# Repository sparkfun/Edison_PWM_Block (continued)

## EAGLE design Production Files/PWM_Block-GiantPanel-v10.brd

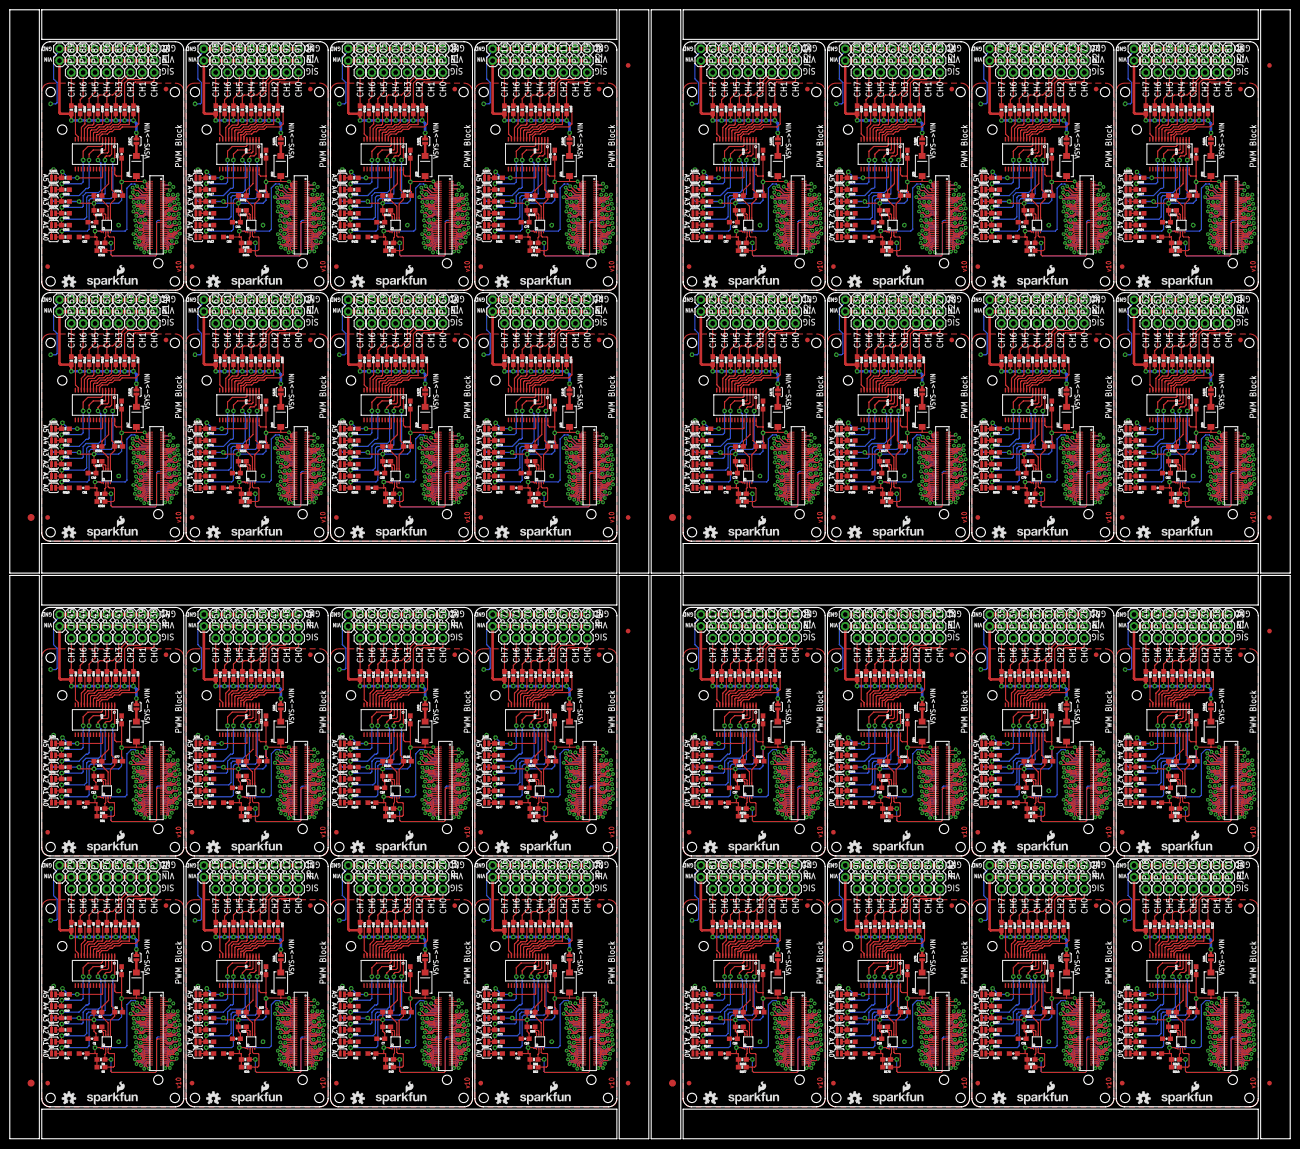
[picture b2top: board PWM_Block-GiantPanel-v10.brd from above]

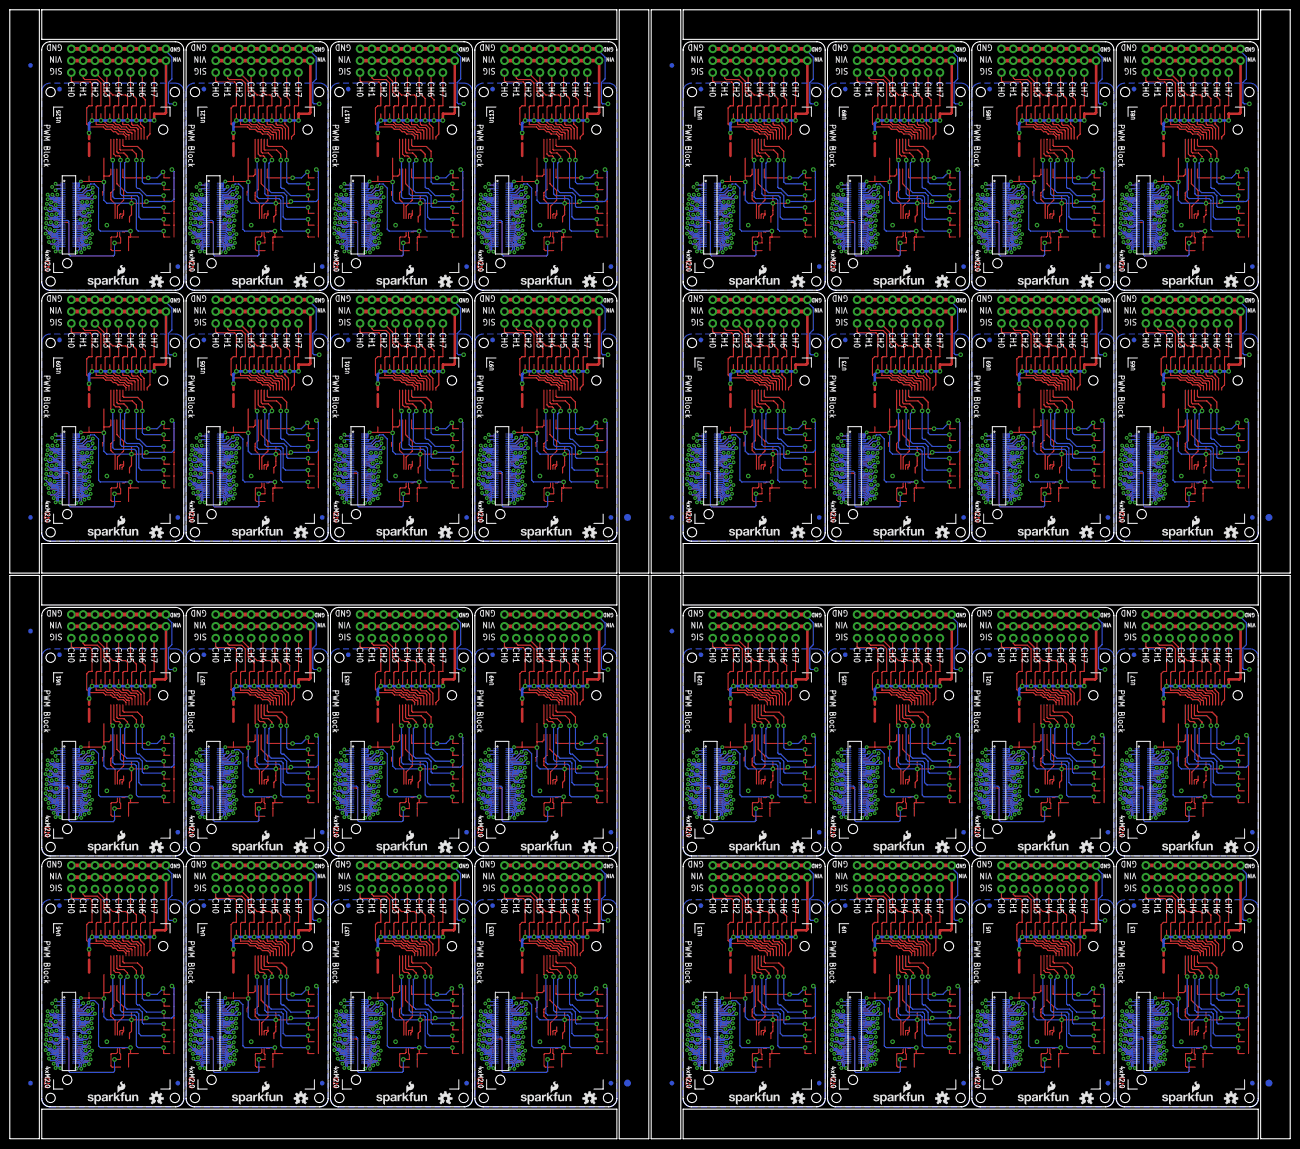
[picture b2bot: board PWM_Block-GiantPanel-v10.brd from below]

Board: 2 copper layers, 274.8 x 242.3 mm, 1656 parts (204 on the bottom side), 2464 nets.

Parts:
C1, C2, C3, C4, C5, C6, C7, C8, C9, C10, C11, C12, C13, C14, C15, C16, C17, C18, C19, C20, C21, C22, C23, C24, C25, C26, C27, C28, C29, C30, C31, C32, C33, C34, C35, C36, C37, C38, C39, C40, C41, C42, C43, C44, C45, C46, C47, C48, C49, C50, C51, C52, C53, C54, C55, C56, C57, C58, C59, C60, C61, C62, C63, C64, C65, C66, C67, C68, C69, C70, C71, C72, C73, C74, C75, C76, C77, C78, C79, C80, C81, C82, C83, C84, C85, C86, C87, C88, C89, C90, C91, C92, C93, C94, C95, C96: 0.1uF; 0603-CAP
D1, D2, D3, D4, D5, D6, D7, D8, D9, D10, D11, D12, D13, D14, D15, D16, D17, D18, D19, D20, D21, D22, D23, D24, D25, D26, D27, D28, D29, D30, D31, D32: B340A; SMA-DIODE
E$1, E$2, E$9, E$10, E$15, E$16, E$21, E$22: FIDUCIAL-1.5X3
E$3, E$4, E$5, E$6, E$7, E$8, E$11, E$12, E$13, E$14, E$17, E$18, E$19, E$20, E$23, E$24: FIDUCIAL-1X2
FID1, FID2, FID3, FID4, FID5, FID6, FID7, FID8, FID9, FID10, FID11, FID12, FID13, FID14, FID15, FID16, FID17, FID18, FID19, FID20, FID21, FID22, FID23, FID24, FID25, FID26, FID27, FID28, FID29, FID30, FID31, FID32, FID33, FID34, FID35, FID36, FID37, FID38, FID39, FID40, FID41, FID42, FID43, FID44, FID45, FID46, FID47, FID48, FID49, FID50, FID51, FID52, FID53, FID54, FID55, FID56, FID57, FID58, FID59, FID60, FID61, FID62, FID63, FID64, FID65, FID66, FID67, FID68, FID69, FID70, FID71, FID72, FID73, FID74, FID75, FID76, FID77, FID78, FID79, FID80, FID81, FID82, FID83, FID84, FID85, FID86, FID87, FID88, FID89, FID90, FID91, FID92, FID93, FID94, FID95, FID96, FID97, FID98, FID99, FID100, FID101, FID102, FID103, FID104, FID105, FID106, FID107, FID108, FID109, FID110, FID111, FID112, FID113, FID114, FID115, FID116, FID117, FID118, FID119, FID120, FID121, FID122, FID123, FID124, FID125, FID126, FID127, FID128: FIDUCIAL1X2; FIDUCIAL-1X2
JP1, JP2, JP3, JP4, JP5, JP6, JP7, JP8, JP10, JP11, JP12, JP13, JP14, JP15, JP16, JP17, JP19, JP20, JP21, JP22, JP23, JP24, JP25, JP26, JP28, JP29, JP30, JP31, JP32, JP33, JP34, JP35, JP37, JP38, JP39, JP40, JP41, JP42, JP43, JP44, JP46, JP47, JP48, JP49, JP50, JP51, JP52, JP53, JP55, JP56, JP57, JP58, JP59, JP60, JP61, JP62, JP64, JP65, JP66, JP67, JP68, JP69, JP70, JP71, JP73, JP74, JP75, JP76, JP77, JP78, JP79, JP80, JP82, JP83, JP84, JP85, JP86, JP87, JP88, JP89, JP91, JP92, JP93, JP94, JP95, JP96, JP97, JP98, JP100, JP101, JP102, JP103, JP104, JP105, JP106, JP107, JP109, JP110, JP111, JP112, JP113, JP114, JP115, JP116, JP118, JP119, JP120, JP121, JP122, JP123, JP124, JP125, JP127, JP128, JP129, JP130, JP131, JP132, JP133, JP134, JP136, JP137, JP138, JP139, JP140, JP141, JP142, JP143, JP145, JP146, JP147, JP148, JP149, JP150, JP151, JP152, JP154, JP155, JP156, JP157, JP158, JP159, JP160, JP161, JP163, JP164, JP165, JP166, JP167, JP168, JP169, JP170, JP172, JP173, JP174, JP175, JP176, JP177, JP178, JP179, JP181, JP182, JP183, JP184, JP185, JP186, JP187, JP188, JP190, JP191, JP192, JP193, JP194, JP195, JP196, JP197, JP199, JP200, JP201, JP202, JP203, JP204, JP205, JP206, JP208, JP209, JP210, JP211, JP212, JP213, JP214, JP215, JP217, JP218, JP219, JP220, JP221, JP222, JP223, JP224, JP226, JP227, JP228, JP229, JP230, JP231, JP232, JP233, JP235, JP236, JP237, JP238, JP239, JP240, JP241, JP242, JP244, JP245, JP246, JP247, JP248, JP249, JP250, JP251, JP253, JP254, JP255, JP256, JP257, JP258, JP259, JP260, JP262, JP263, JP264, JP265, JP266, JP267, JP268, JP269, JP271, JP272, JP273, JP274, JP275, JP276, JP277, JP278, JP280, JP281, JP282, JP283, JP284, JP285, JP286, JP287: 1X03
JP9, JP18, JP27, JP36, JP45, JP54, JP63, JP72, JP81, JP90, JP99, JP108, JP117, JP126, JP135, JP144, JP153, JP162, JP171, JP180, JP189, JP198, JP207, JP216, JP225, JP234, JP243, JP252, JP261, JP270, JP279, JP288: M02PTH; 1X02
LOGO1, LOGO3, LOGO6, LOGO7, LOGO10, LOGO11, LOGO14, LOGO15, LOGO18, LOGO19, LOGO22, LOGO23, LOGO26, LOGO27, LOGO30, LOGO31, LOGO34, LOGO35, LOGO38, LOGO39, LOGO42, LOGO43, LOGO46, LOGO47, LOGO50, LOGO51, LOGO54, LOGO55, LOGO58, LOGO59, LOGO62, LOGO63, LOGO66, LOGO67, LOGO70, LOGO71, LOGO74, LOGO75, LOGO78, LOGO79, LOGO82, LOGO83, LOGO86, LOGO87, LOGO90, LOGO91, LOGO94, LOGO95, LOGO98, LOGO99, LOGO102, LOGO103, LOGO106, LOGO107, LOGO110, LOGO111, LOGO114, LOGO115, LOGO118, LOGO119, LOGO122, LOGO123, LOGO126, LOGO127: SFE_LOGO_NAME_FLAME.1_INCH; SFE_LOGO_NAME_FLAME_.1
LOGO2, LOGO4, LOGO5, LOGO8, LOGO9, LOGO12, LOGO13, LOGO16, LOGO17, LOGO20, LOGO21, LOGO24, LOGO25, LOGO28, LOGO29, LOGO32, LOGO33, LOGO36, LOGO37, LOGO40, LOGO41, LOGO44, LOGO45, LOGO48, LOGO49, LOGO52, LOGO53, LOGO56, LOGO57, LOGO60, LOGO61, LOGO64, LOGO65, LOGO68, LOGO69, LOGO72, LOGO73, LOGO76, LOGO77, LOGO80, LOGO81, LOGO84, LOGO85, LOGO88, LOGO89, LOGO92, LOGO93, LOGO96, LOGO97, LOGO100, LOGO101, LOGO104, LOGO105, LOGO108, LOGO109, LOGO112, LOGO113, LOGO116, LOGO117, LOGO120, LOGO121, LOGO124, LOGO125, LOGO128: OSHW-LOGOS; OSHW-LOGO-S
R1, R2, R20, R21, R39, R40, R58, R59, R77, R78, R96, R97, R115, R116, R134, R135, R153, R154, R172, R173, R191, R192, R210, R211, R229, R230, R248, R249, R267, R268, R286, R287, R305, R306, R324, R325, R343, R344, R362, R363, R381, R382, R400, R401, R419, R420, R438, R439, R457, R458, R476, R477, R495, R496, R514, R515, R533, R534, R552, R553, R571, R572, R590, R591: 10K; 0603-RES
R3, R22, R41, R60, R79, R98, R117, R136, R155, R174, R193, R212, R231, R250, R269, R288, R307, R326, R345, R364, R383, R402, R421, R440, R459, R478, R497, R516, R535, R554, R573, R592: 200k; 0603-RES
R4, R5, R23, R24, R42, R43, R61, R62, R80, R81, R99, R100, R118, R119, R137, R138, R156, R157, R175, R176, R194, R195, R213, R214, R232, R233, R251, R252, R270, R271, R289, R290, R308, R309, R327, R328, R346, R347, R365, R366, R384, R385, R403, R404, R422, R423, R441, R442, R460, R461, R479, R480, R498, R499, R517, R518, R536, R537, R555, R556, R574, R575, R593, R594: DNP; 0603-RES
R6, R7, R8, R9, R10, R11, R12, R13, R14, R15, R16, R17, R18, R19, R25, R26, R27, R28, R29, R30, R31, R32, R33, R34, R35, R36, R37, R38, R44, R45, R46, R47, R48, R49, R50, R51, R52, R53, R54, R55, R56, R57, R63, R64, R65, R66, R67, R68, R69, R70, R71, R72, R73, R74, R75, R76, R82, R83, R84, R85, R86, R87, R88, R89, R90, R91, R92, R93, R94, R95, R101, R102, R103, R104, R105, R106, R107, R108, R109, R110, R111, R112, R113, R114, R120, R121, R122, R123, R124, R125, R126, R127, R128, R129, R130, R131, R132, R133, R139, R140, R141, R142, R143, R144, R145, R146, R147, R148, R149, R150, R151, R152, R158, R159, R160, R161, R162, R163, R164, R165, R166, R167, R168, R169, R170, R171, R177, R178, R179, R180, R181, R182, R183, R184, R185, R186, R187, R188, R189, R190, R196, R197, R198, R199, R200, R201, R202, R203, R204, R205, R206, R207, R208, R209, R215, R216, R217, R218, R219, R220, R221, R222, R223, R224, R225, R226, R227, R228, R234, R235, R236, R237, R238, R239, R240, R241, R242, R243, R244, R245, R246, R247, R253, R254, R255, R256, R257, R258, R259, R260, R261, R262, R263, R264, R265, R266, R272, R273, R274, R275, R276, R277, R278, R279, R280, R281, R282, R283, R284, R285, R291, R292, R293, R294, R295, R296, R297, R298, R299, R300, R301, R302, R303, R304, R310, R311, R312, R313, R314, R315, R316, R317, R318, R319, R320, R321, R322, R323, R329, R330, R331, R332, R333, R334, R335, R336, R337, R338, R339, R340, R341, R342, R348, R349, R350, R351, R352, R353, R354, R355, R356, R357, R358, R359, R360, R361, R367, R368, R369, R370, R371, R372, R373, R374, R375, R376, R377, R378, R379, R380, R386, R387, R388, R389, R390, R391, R392, R393, R394, R395, R396, R397, R398, R399, R405, R406, R407, R408, R409, R410, R411, R412, R413, R414, R415, R416, R417, R418, R424, R425, R426, R427, R428, R429, R430, R431, R432, R433, R434, R435, R436, R437, R443, R444, R445, R446, R447, R448, R449, R450, R451, R452, R453, R454, R455, R456, R462, R463, R464, R465, R466, R467, R468, R469, R470, R471, R472, R473, R474, R475, R481, R482, R483, R484, R485, R486, R487, R488, R489, R490, R491, R492, R493, R494, R500, R501, R502, R503, R504, R505, R506, R507, R508, R509, R510, R511, R512, R513, R519, R520, R521, R522, R523, R524, R525, R526, R527, R528, R529, R530, R531, R532, R538, R539, R540, R541, R542, R543, R544, R545, R546, R547, R548, R549, R550, R551, R557, R558, R559, R560, R561, R562, R563, R564, R565, R566, R567, R568, R569, R570, R576, R577, R578, R579, R580, R581, R582, R583, R584, R585, R586, R587, R588, R589, R595, R596, R597, R598, R599, R600, R601, R602, R603, R604, R605, R606, R607, R608: 1K; 0603-RES
SJ1, SJ2, SJ3, SJ4, SJ5, SJ6, SJ8, SJ9, SJ10, SJ11, SJ12, SJ13, SJ15, SJ16, SJ17, SJ18, SJ19, SJ20, SJ22, SJ23, SJ24, SJ25, SJ26, SJ27, SJ29, SJ30, SJ31, SJ32, SJ33, SJ34, SJ36, SJ37, SJ38, SJ39, SJ40, SJ41, SJ43, SJ44, SJ45, SJ46, SJ47, SJ48, SJ50, SJ51, SJ52, SJ53, SJ54, SJ55, SJ57, SJ58, SJ59, SJ60, SJ61, SJ62, SJ64, SJ65, SJ66, SJ67, SJ68, SJ69, SJ71, SJ72, SJ73, SJ74, SJ75, SJ76, SJ78, SJ79, SJ80, SJ81, SJ82, SJ83, SJ85, SJ86, SJ87, SJ88, SJ89, SJ90, SJ92, SJ93, SJ94, SJ95, SJ96, SJ97, SJ99, SJ100, SJ101, SJ102, SJ103, SJ104, SJ106, SJ107, SJ108, SJ109, SJ110, SJ111, SJ113, SJ114, SJ115, SJ116, SJ117, SJ118, SJ120, SJ121, SJ122, SJ123, SJ124, SJ125, SJ127, SJ128, SJ129, SJ130, SJ131, SJ132, SJ134, SJ135, SJ136, SJ137, SJ138, SJ139, SJ141, SJ142, SJ143, SJ144, SJ145, SJ146, SJ148, SJ149, SJ150, SJ151, SJ152, SJ153, SJ155, SJ156, SJ157, SJ158, SJ159, SJ160, SJ162, SJ163, SJ164, SJ165, SJ166, SJ167, SJ169, SJ170, SJ171, SJ172, SJ173, SJ174, SJ176, SJ177, SJ178, SJ179, SJ180, SJ181, SJ183, SJ184, SJ185, SJ186, SJ187, SJ188, SJ190, SJ191, SJ192, SJ193, SJ194, SJ195, SJ197, SJ198, SJ199, SJ200, SJ201, SJ202, SJ204, SJ205, SJ206, SJ207, SJ208, SJ209, SJ211, SJ212, SJ213, SJ214, SJ215, SJ216, SJ218, SJ219, SJ220, SJ221, SJ222, SJ223: JUMPER-PAD-2-NOYES_SILK; PAD-JUMPER-2-NO_YES_SILK
SJ7, SJ14, SJ21, SJ28, SJ35, SJ42, SJ49, SJ56, SJ63, SJ70, SJ77, SJ84, SJ91, SJ98, SJ105, SJ112, SJ119, SJ126, SJ133, SJ140, SJ147, SJ154, SJ161, SJ168, SJ175, SJ182, SJ189, SJ196, SJ203, SJ210, SJ217, SJ224: VIN_ENABLE; PAD-JUMPER-2-NO_YES_SILK
U1, U8, U12, U16, U20, U24, U28, U32, U36, U40, U44, U48, U52, U56, U60, U64, U68, U72, U76, U80, U84, U88, U92, U96, U100, U104, U108, U112, U116, U120, U124, U128: PCA9685; TSSOP-28_4MM
U2, U7, U11, U15, U19, U23, U27, U31, U35, U39, U43, U47, U51, U55, U59, U63, U67, U71, U75, U79, U83, U87, U91, U95, U99, U103, U107, U111, U115, U119, U123, U127: PCA9306; PCA9306DC-1:1
U3, U5, U9, U13, U17, U21, U25, U29, U33, U37, U41, U45, U49, U53, U57, U61, U65, U69, U73, U77, U81, U85, U89, U93, U97, U101, U105, U109, U113, U117, U121, U125: EDISON_CONNECTOR_FULLMOUNTING_HOLES; EDISON_DAUGHTER
U4, U6, U10, U14, U18, U22, U26, U30, U34, U38, U42, U46, U50, U54, U58, U62, U66, U70, U74, U78, U82, U86, U90, U94, U98, U102, U106, U110, U114, U118, U122, U126: EDISON_CONNECTOR_FULLHEADER; DF40C-70DP-0.4(51)

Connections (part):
1.8V: C3.1, R4.2, R5.2, U2.1, U3.12, U4.12
1.8V1: C6.1, R23.2, R24.2, U5.12, U6.12, U7.1
1.8V2: C9.1, R42.2, R43.2, U9.12, U10.12, U11.1
1.8V3: C12.1, R61.2, R62.2, U13.12, U14.12, U15.1
1.8V4: C15.1, R80.2, R81.2, U17.12, U18.12, U19.1
1.8V5: C18.1, R99.2, R100.2, U21.12, U22.12, U23.1
1.8V6: C21.1, R118.2, R119.2, U25.12, U26.12, U27.1
1.8V7: C24.1, R137.2, R138.2, U29.12, U30.12, U31.1
1.8V8: C27.1, R156.2, R157.2, U33.12, U34.12, U35.1
1.8V9: C30.1, R175.2, R176.2, U37.12, U38.12, U39.1
1.8V10: C33.1, R194.2, R195.2, U41.12, U42.12, U43.1
1.8V11: C36.1, R213.2, R214.2, U45.12, U46.12, U47.1
1.8V12: C39.1, R232.2, R233.2, U49.12, U50.12, U51.1
1.8V13: C42.1, R251.2, R252.2, U53.12, U54.12, U55.1
1.8V14: C45.1, R270.2, R271.2, U57.12, U58.12, U59.1
1.8V15: C48.1, R289.2, R290.2, U61.12, U62.12, U63.1
1.8V16: C51.1, R308.2, R309.2, U65.12, U66.12, U67.1
1.8V17: C54.1, R327.2, R328.2, U69.12, U70.12, U71.1
1.8V18: C57.1, R346.2, R347.2, U73.12, U74.12, U75.1
1.8V19: C60.1, R365.2, R366.2, U77.12, U78.12, U79.1
1.8V20: C63.1, R384.2, R385.2, U81.12, U82.12, U83.1
1.8V21: C66.1, R403.2, R404.2, U85.12, U86.12, U87.1
1.8V22: C69.1, R422.2, R423.2, U89.12, U90.12, U91.1
1.8V23: C72.1, R441.2, R442.2, U93.12, U94.12, U95.1
1.8V24: C75.1, R460.2, R461.2, U97.12, U98.12, U99.1
1.8V25: C78.1, R479.2, R480.2, U101.12, U102.12, U103.1
1.8V26: C81.1, R498.2, R499.2, U105.12, U106.12, U107.1
1.8V27: C84.1, R517.2, R518.2, U109.12, U110.12, U111.1
1.8V28: C87.1, R536.2, R537.2, U113.12, U114.12, U115.1
1.8V29: C90.1, R555.2, R556.2, U117.12, U118.12, U119.1
1.8V30: C93.1, R574.2, R575.2, U121.12, U122.12, U123.1
1.8V31: C96.1, R593.2, R594.2, U125.12, U126.12, U127.1
3.3V: U3.8, U3.10, U4.8, U4.10
3.3V1: U5.8, U5.10, U6.8, U6.10
3.3V2: U9.8, U9.10, U10.8, U10.10
3.3V3: U13.8, U13.10, U14.8, U14.10
3.3V4: U17.8, U17.10, U18.8, U18.10
3.3V5: U21.8, U21.10, U22.8, U22.10
3.3V6: U25.8, U25.10, U26.8, U26.10
3.3V7: U29.8, U29.10, U30.8, U30.10
3.3V8: U33.8, U33.10, U34.8, U34.10
3.3V9: U37.8, U37.10, U38.8, U38.10
3.3V10: U41.8, U41.10, U42.8, U42.10
3.3V11: U45.8, U45.10, U46.8, U46.10
3.3V12: U49.8, U49.10, U50.8, U50.10
3.3V13: U53.8, U53.10, U54.8, U54.10
3.3V14: U57.8, U57.10, U58.8, U58.10
3.3V15: U61.8, U61.10, U62.8, U62.10
3.3V16: U65.8, U65.10, U66.8, U66.10
3.3V17: U69.8, U69.10, U70.8, U70.10
3.3V18: U73.8, U73.10, U74.8, U74.10
3.3V19: U77.8, U77.10, U78.8, U78.10
3.3V20: U81.8, U81.10, U82.8, U82.10
3.3V21: U85.8, U85.10, U86.8, U86.10
3.3V22: U89.8, U89.10, U90.8, U90.10
3.3V23: U93.8, U93.10, U94.8, U94.10
3.3V24: U97.8, U97.10, U98.8, U98.10
3.3V25: U101.8, U101.10, U102.8, U102.10
3.3V26: U105.8, U105.10, U106.8, U106.10
3.3V27: U109.8, U109.10, U110.8, U110.10
3.3V28: U113.8, U113.10, U114.8, U114.10
3.3V29: U117.8, U117.10, U118.8, U118.10
3.3V30: U121.8, U121.10, U122.8, U122.10
3.3V31: U125.8, U125.10, U126.8, U126.10
A0: R14.2, SJ1.2, U1.1
A1: R15.2, SJ2.2, U1.2
A2: R16.2, SJ3.2, U1.3
A3: R17.2, SJ4.2, U1.4
A4: R18.2, SJ5.2, U1.5
A5: R19.2, SJ6.2, U1.24
A6: R37.2, SJ12.2, U8.5
A7: R36.2, SJ11.2, U8.4
A8: R35.2, SJ10.2, U8.3
A9: R34.2, SJ9.2, U8.2
A10: R33.2, SJ8.2, U8.1
A11: R38.2, SJ13.2, U8.24
A12: R56.2, SJ19.2, U12.5
A13: R55.2, SJ18.2, U12.4
A14: R54.2, SJ17.2, U12.3
A15: R53.2, SJ16.2, U12.2
A16: R52.2, SJ15.2, U12.1
A17: R57.2, SJ20.2, U12.24
A18: R75.2, SJ26.2, U16.5
A19: R74.2, SJ25.2, U16.4
A20: R73.2, SJ24.2, U16.3
A21: R72.2, SJ23.2, U16.2
A22: R71.2, SJ22.2, U16.1
A23: R76.2, SJ27.2, U16.24
A24: R94.2, SJ33.2, U20.5
A25: R93.2, SJ32.2, U20.4
A26: R92.2, SJ31.2, U20.3
A27: R91.2, SJ30.2, U20.2
A28: R90.2, SJ29.2, U20.1
A29: R95.2, SJ34.2, U20.24
A30: R113.2, SJ40.2, U24.5
A31: R112.2, SJ39.2, U24.4
A32: R111.2, SJ38.2, U24.3
A33: R110.2, SJ37.2, U24.2
A34: R109.2, SJ36.2, U24.1
A35: R114.2, SJ41.2, U24.24
A36: R132.2, SJ47.2, U28.5
A37: R131.2, SJ46.2, U28.4
A38: R130.2, SJ45.2, U28.3
A39: R129.2, SJ44.2, U28.2
A40: R128.2, SJ43.2, U28.1
A41: R133.2, SJ48.2, U28.24
A42: R151.2, SJ54.2, U32.5
A43: R150.2, SJ53.2, U32.4
A44: R149.2, SJ52.2, U32.3
A45: R148.2, SJ51.2, U32.2
A46: R147.2, SJ50.2, U32.1
A47: R152.2, SJ55.2, U32.24
A48: R170.2, SJ61.2, U36.5
A49: R169.2, SJ60.2, U36.4
A50: R168.2, SJ59.2, U36.3
A51: R167.2, SJ58.2, U36.2
A52: R166.2, SJ57.2, U36.1
A53: R171.2, SJ62.2, U36.24
A54: R189.2, SJ68.2, U40.5
A55: R188.2, SJ67.2, U40.4
A56: R187.2, SJ66.2, U40.3
A57: R186.2, SJ65.2, U40.2
A58: R185.2, SJ64.2, U40.1
A59: R190.2, SJ69.2, U40.24
A60: R208.2, SJ75.2, U44.5
A61: R207.2, SJ74.2, U44.4
A62: R206.2, SJ73.2, U44.3
A63: R205.2, SJ72.2, U44.2
A64: R204.2, SJ71.2, U44.1
A65: R209.2, SJ76.2, U44.24
A66: R227.2, SJ82.2, U48.5
A67: R226.2, SJ81.2, U48.4
A68: R225.2, SJ80.2, U48.3
A69: R224.2, SJ79.2, U48.2
A70: R223.2, SJ78.2, U48.1
A71: R228.2, SJ83.2, U48.24
A72: R246.2, SJ89.2, U52.5
A73: R245.2, SJ88.2, U52.4
A74: R244.2, SJ87.2, U52.3
A75: R243.2, SJ86.2, U52.2
A76: R242.2, SJ85.2, U52.1
A77: R247.2, SJ90.2, U52.24
A78: R265.2, SJ96.2, U56.5
A79: R264.2, SJ95.2, U56.4
A80: R263.2, SJ94.2, U56.3
A81: R262.2, SJ93.2, U56.2
A82: R261.2, SJ92.2, U56.1
A83: R266.2, SJ97.2, U56.24
A84: R284.2, SJ103.2, U60.5
A85: R283.2, SJ102.2, U60.4
A86: R282.2, SJ101.2, U60.3
A87: R281.2, SJ100.2, U60.2
A88: R280.2, SJ99.2, U60.1
A89: R285.2, SJ104.2, U60.24
A90: R303.2, SJ110.2, U64.5
A91: R302.2, SJ109.2, U64.4
A92: R301.2, SJ108.2, U64.3
A93: R300.2, SJ107.2, U64.2
A94: R299.2, SJ106.2, U64.1
A95: R304.2, SJ111.2, U64.24
A96: R322.2, SJ117.2, U68.5
A97: R321.2, SJ116.2, U68.4
A98: R320.2, SJ115.2, U68.3
A99: R319.2, SJ114.2, U68.2
A100: R318.2, SJ113.2, U68.1
A101: R323.2, SJ118.2, U68.24
A102: R341.2, SJ124.2, U72.5
A103: R340.2, SJ123.2, U72.4
A104: R339.2, SJ122.2, U72.3
A105: R338.2, SJ121.2, U72.2
A106: R337.2, SJ120.2, U72.1
A107: R342.2, SJ125.2, U72.24
A108: R360.2, SJ131.2, U76.5
A109: R359.2, SJ130.2, U76.4
A110: R358.2, SJ129.2, U76.3
A111: R357.2, SJ128.2, U76.2
A112: R356.2, SJ127.2, U76.1
A113: R361.2, SJ132.2, U76.24
A114: R379.2, SJ138.2, U80.5
A115: R378.2, SJ137.2, U80.4
A116: R377.2, SJ136.2, U80.3
A117: R376.2, SJ135.2, U80.2
A118: R375.2, SJ134.2, U80.1
A119: R380.2, SJ139.2, U80.24
A120: R398.2, SJ145.2, U84.5
A121: R397.2, SJ144.2, U84.4
A122: R396.2, SJ143.2, U84.3
A123: R395.2, SJ142.2, U84.2
A124: R394.2, SJ141.2, U84.1
A125: R399.2, SJ146.2, U84.24
A126: R417.2, SJ152.2, U88.5
A127: R416.2, SJ151.2, U88.4
A128: R415.2, SJ150.2, U88.3
A129: R414.2, SJ149.2, U88.2
A130: R413.2, SJ148.2, U88.1
A131: R418.2, SJ153.2, U88.24
A132: R436.2, SJ159.2, U92.5
A133: R435.2, SJ158.2, U92.4
A134: R434.2, SJ157.2, U92.3
A135: R433.2, SJ156.2, U92.2
A136: R432.2, SJ155.2, U92.1
A137: R437.2, SJ160.2, U92.24
A138: R455.2, SJ166.2, U96.5
A139: R454.2, SJ165.2, U96.4
A140: R453.2, SJ164.2, U96.3
A141: R452.2, SJ163.2, U96.2
A142: R451.2, SJ162.2, U96.1
A143: R456.2, SJ167.2, U96.24
A144: R474.2, SJ173.2, U100.5
A145: R473.2, SJ172.2, U100.4
A146: R472.2, SJ171.2, U100.3
A147: R471.2, SJ170.2, U100.2
A148: R470.2, SJ169.2, U100.1
A149: R475.2, SJ174.2, U100.24
A150: R493.2, SJ180.2, U104.5
A151: R492.2, SJ179.2, U104.4
A152: R491.2, SJ178.2, U104.3
A153: R490.2, SJ177.2, U104.2
A154: R489.2, SJ176.2, U104.1
A155: R494.2, SJ181.2, U104.24
A156: R512.2, SJ187.2, U108.5
A157: R511.2, SJ186.2, U108.4
A158: R510.2, SJ185.2, U108.3
A159: R509.2, SJ184.2, U108.2
A160: R508.2, SJ183.2, U108.1
A161: R513.2, SJ188.2, U108.24
A162: R531.2, SJ194.2, U112.5
A163: R530.2, SJ193.2, U112.4
A164: R529.2, SJ192.2, U112.3
A165: R528.2, SJ191.2, U112.2
A166: R527.2, SJ190.2, U112.1
A167: R532.2, SJ195.2, U112.24
A168: R550.2, SJ201.2, U116.5
A169: R549.2, SJ200.2, U116.4
A170: R548.2, SJ199.2, U116.3
A171: R547.2, SJ198.2, U116.2
A172: R546.2, SJ197.2, U116.1
A173: R551.2, SJ202.2, U116.24
A174: R569.2, SJ208.2, U120.5
A175: R568.2, SJ207.2, U120.4
A176: R567.2, SJ206.2, U120.3
A177: R566.2, SJ205.2, U120.2
A178: R565.2, SJ204.2, U120.1
A179: R570.2, SJ209.2, U120.24
A180: R588.2, SJ215.2, U124.5
A181: R587.2, SJ214.2, U124.4
A182: R586.2, SJ213.2, U124.3
A183: R585.2, SJ212.2, U124.2
A184: R584.2, SJ211.2, U124.1
A185: R589.2, SJ216.2, U124.24
A186: R607.2, SJ222.2, U128.5
A187: R606.2, SJ221.2, U128.4
A188: R605.2, SJ220.2, U128.3
A189: R604.2, SJ219.2, U128.2
A190: R603.2, SJ218.2, U128.1
A191: R608.2, SJ223.2, U128.24
CH0: JP1.3, R13.1, U1.6
CH1: JP2.3, R12.1, U1.7
CH2: JP3.3, R11.1, U1.8
CH3: JP4.3, R10.1, U1.9
CH4: JP5.3, R9.1, U1.10
CH5: JP6.3, R8.1, U1.11
CH6: JP7.3, R7.1, U1.12
CH7: JP8.3, R6.1, U1.13
CH8: JP10.3, R32.1, U8.6
CH9: JP11.3, R31.1, U8.7
CH10: JP12.3, R30.1, U8.8
CH11: JP13.3, R29.1, U8.9
CH12: JP14.3, R28.1, U8.10
CH13: JP15.3, R27.1, U8.11
CH14: JP16.3, R26.1, U8.12
CH15: JP17.3, R25.1, U8.13
CH16: JP19.3, R51.1, U12.6
CH17: JP20.3, R50.1, U12.7
CH18: JP21.3, R49.1, U12.8
CH19: JP22.3, R48.1, U12.9
CH20: JP23.3, R47.1, U12.10
CH21: JP24.3, R46.1, U12.11
CH22: JP25.3, R45.1, U12.12
CH23: JP26.3, R44.1, U12.13
CH24: JP28.3, R70.1, U16.6
CH25: JP29.3, R69.1, U16.7
CH26: JP30.3, R68.1, U16.8
CH27: JP31.3, R67.1, U16.9
CH28: JP32.3, R66.1, U16.10
CH29: JP33.3, R65.1, U16.11
CH30: JP34.3, R64.1, U16.12
CH31: JP35.3, R63.1, U16.13
CH32: JP37.3, R89.1, U20.6
CH33: JP38.3, R88.1, U20.7
CH34: JP39.3, R87.1, U20.8
CH35: JP40.3, R86.1, U20.9
CH36: JP41.3, R85.1, U20.10
CH37: JP42.3, R84.1, U20.11
CH38: JP43.3, R83.1, U20.12
CH39: JP44.3, R82.1, U20.13
CH40: JP46.3, R108.1, U24.6
CH41: JP47.3, R107.1, U24.7
CH42: JP48.3, R106.1, U24.8
CH43: JP49.3, R105.1, U24.9
CH44: JP50.3, R104.1, U24.10
CH45: JP51.3, R103.1, U24.11
CH46: JP52.3, R102.1, U24.12
CH47: JP53.3, R101.1, U24.13
CH48: JP55.3, R127.1, U28.6
CH49: JP56.3, R126.1, U28.7
CH50: JP57.3, R125.1, U28.8
CH51: JP58.3, R124.1, U28.9
CH52: JP59.3, R123.1, U28.10
CH53: JP60.3, R122.1, U28.11
CH54: JP61.3, R121.1, U28.12
CH55: JP62.3, R120.1, U28.13
CH56: JP64.3, R146.1, U32.6
CH57: JP65.3, R145.1, U32.7
CH58: JP66.3, R144.1, U32.8
CH59: JP67.3, R143.1, U32.9
CH60: JP68.3, R142.1, U32.10
CH61: JP69.3, R141.1, U32.11
CH62: JP70.3, R140.1, U32.12
CH63: JP71.3, R139.1, U32.13
CH64: JP73.3, R165.1, U36.6
CH65: JP74.3, R164.1, U36.7
CH66: JP75.3, R163.1, U36.8
CH67: JP76.3, R162.1, U36.9
CH68: JP77.3, R161.1, U36.10
CH69: JP78.3, R160.1, U36.11
CH70: JP79.3, R159.1, U36.12
CH71: JP80.3, R158.1, U36.13
CH72: JP82.3, R184.1, U40.6
CH73: JP83.3, R183.1, U40.7
CH74: JP84.3, R182.1, U40.8
CH75: JP85.3, R181.1, U40.9
CH76: JP86.3, R180.1, U40.10
CH77: JP87.3, R179.1, U40.11
CH78: JP88.3, R178.1, U40.12
CH79: JP89.3, R177.1, U40.13
CH80: JP91.3, R203.1, U44.6
CH81: JP92.3, R202.1, U44.7
CH82: JP93.3, R201.1, U44.8
CH83: JP94.3, R200.1, U44.9
CH84: JP95.3, R199.1, U44.10
CH85: JP96.3, R198.1, U44.11
CH86: JP97.3, R197.1, U44.12
CH87: JP98.3, R196.1, U44.13
CH88: JP100.3, R222.1, U48.6
CH89: JP101.3, R221.1, U48.7
CH90: JP102.3, R220.1, U48.8
CH91: JP103.3, R219.1, U48.9
CH92: JP104.3, R218.1, U48.10
CH93: JP105.3, R217.1, U48.11
CH94: JP106.3, R216.1, U48.12
CH95: JP107.3, R215.1, U48.13
CH96: JP109.3, R241.1, U52.6
CH97: JP110.3, R240.1, U52.7
CH98: JP111.3, R239.1, U52.8
CH99: JP112.3, R238.1, U52.9
CH100: JP113.3, R237.1, U52.10
CH101: JP114.3, R236.1, U52.11
CH102: JP115.3, R235.1, U52.12
CH103: JP116.3, R234.1, U52.13
CH104: JP118.3, R260.1, U56.6
CH105: JP119.3, R259.1, U56.7
CH106: JP120.3, R258.1, U56.8
CH107: JP121.3, R257.1, U56.9
CH108: JP122.3, R256.1, U56.10
CH109: JP123.3, R255.1, U56.11
CH110: JP124.3, R254.1, U56.12
CH111: JP125.3, R253.1, U56.13
CH112: JP127.3, R279.1, U60.6
CH113: JP128.3, R278.1, U60.7
CH114: JP129.3, R277.1, U60.8
CH115: JP130.3, R276.1, U60.9
CH116: JP131.3, R275.1, U60.10
CH117: JP132.3, R274.1, U60.11
CH118: JP133.3, R273.1, U60.12
CH119: JP134.3, R272.1, U60.13
CH120: JP136.3, R298.1, U64.6
CH121: JP137.3, R297.1, U64.7
CH122: JP138.3, R296.1, U64.8
CH123: JP139.3, R295.1, U64.9
CH124: JP140.3, R294.1, U64.10
CH125: JP141.3, R293.1, U64.11
CH126: JP142.3, R292.1, U64.12
CH127: JP143.3, R291.1, U64.13
CH128: JP145.3, R317.1, U68.6
CH129: JP146.3, R316.1, U68.7
CH130: JP147.3, R315.1, U68.8
CH131: JP148.3, R314.1, U68.9
CH132: JP149.3, R313.1, U68.10
CH133: JP150.3, R312.1, U68.11
CH134: JP151.3, R311.1, U68.12
CH135: JP152.3, R310.1, U68.13
CH136: JP154.3, R336.1, U72.6
CH137: JP155.3, R335.1, U72.7
CH138: JP156.3, R334.1, U72.8
CH139: JP157.3, R333.1, U72.9
CH140: JP158.3, R332.1, U72.10
CH141: JP159.3, R331.1, U72.11
CH142: JP160.3, R330.1, U72.12
CH143: JP161.3, R329.1, U72.13
CH144: JP163.3, R355.1, U76.6
CH145: JP164.3, R354.1, U76.7
CH146: JP165.3, R353.1, U76.8
CH147: JP166.3, R352.1, U76.9
CH148: JP167.3, R351.1, U76.10
CH149: JP168.3, R350.1, U76.11
CH150: JP169.3, R349.1, U76.12
CH151: JP170.3, R348.1, U76.13
CH152: JP172.3, R374.1, U80.6
CH153: JP173.3, R373.1, U80.7
CH154: JP174.3, R372.1, U80.8
CH155: JP175.3, R371.1, U80.9
CH156: JP176.3, R370.1, U80.10
CH157: JP177.3, R369.1, U80.11
CH158: JP178.3, R368.1, U80.12
CH159: JP179.3, R367.1, U80.13
CH160: JP181.3, R393.1, U84.6
CH161: JP182.3, R392.1, U84.7
CH162: JP183.3, R391.1, U84.8
CH163: JP184.3, R390.1, U84.9
CH164: JP185.3, R389.1, U84.10
CH165: JP186.3, R388.1, U84.11
CH166: JP187.3, R387.1, U84.12
CH167: JP188.3, R386.1, U84.13
CH168: JP190.3, R412.1, U88.6
CH169: JP191.3, R411.1, U88.7
CH170: JP192.3, R410.1, U88.8
CH171: JP193.3, R409.1, U88.9
CH172: JP194.3, R408.1, U88.10
CH173: JP195.3, R407.1, U88.11
CH174: JP196.3, R406.1, U88.12
CH175: JP197.3, R405.1, U88.13
CH176: JP199.3, R431.1, U92.6
CH177: JP200.3, R430.1, U92.7
CH178: JP201.3, R429.1, U92.8
CH179: JP202.3, R428.1, U92.9
CH180: JP203.3, R427.1, U92.10
CH181: JP204.3, R426.1, U92.11
CH182: JP205.3, R425.1, U92.12
CH183: JP206.3, R424.1, U92.13
CH184: JP208.3, R450.1, U96.6
CH185: JP209.3, R449.1, U96.7
CH186: JP210.3, R448.1, U96.8
CH187: JP211.3, R447.1, U96.9
CH188: JP212.3, R446.1, U96.10
CH189: JP213.3, R445.1, U96.11
CH190: JP214.3, R444.1, U96.12
CH191: JP215.3, R443.1, U96.13
CH192: JP217.3, R469.1, U100.6
CH193: JP218.3, R468.1, U100.7
CH194: JP219.3, R467.1, U100.8
CH195: JP220.3, R466.1, U100.9
CH196: JP221.3, R465.1, U100.10
CH197: JP222.3, R464.1, U100.11
CH198: JP223.3, R463.1, U100.12
CH199: JP224.3, R462.1, U100.13
CH200: JP226.3, R488.1, U104.6
CH201: JP227.3, R487.1, U104.7
CH202: JP228.3, R486.1, U104.8
CH203: JP229.3, R485.1, U104.9
CH204: JP230.3, R484.1, U104.10
CH205: JP231.3, R483.1, U104.11
CH206: JP232.3, R482.1, U104.12
CH207: JP233.3, R481.1, U104.13
CH208: JP235.3, R507.1, U108.6
CH209: JP236.3, R506.1, U108.7
CH210: JP237.3, R505.1, U108.8
CH211: JP238.3, R504.1, U108.9
CH212: JP239.3, R503.1, U108.10
CH213: JP240.3, R502.1, U108.11
CH214: JP241.3, R501.1, U108.12
CH215: JP242.3, R500.1, U108.13
CH216: JP244.3, R526.1, U112.6
CH217: JP245.3, R525.1, U112.7
CH218: JP246.3, R524.1, U112.8
CH219: JP247.3, R523.1, U112.9
CH220: JP248.3, R522.1, U112.10
CH221: JP249.3, R521.1, U112.11
CH222: JP250.3, R520.1, U112.12
CH223: JP251.3, R519.1, U112.13
CH224: JP253.3, R545.1, U116.6
CH225: JP254.3, R544.1, U116.7
CH226: JP255.3, R543.1, U116.8
CH227: JP256.3, R542.1, U116.9
CH228: JP257.3, R541.1, U116.10
CH229: JP258.3, R540.1, U116.11
CH230: JP259.3, R539.1, U116.12
CH231: JP260.3, R538.1, U116.13
CH232: JP262.3, R564.1, U120.6
CH233: JP263.3, R563.1, U120.7
CH234: JP264.3, R562.1, U120.8
CH235: JP265.3, R561.1, U120.9
CH236: JP266.3, R560.1, U120.10
CH237: JP267.3, R559.1, U120.11
CH238: JP268.3, R558.1, U120.12
CH239: JP269.3, R557.1, U120.13
CH240: JP271.3, R583.1, U124.6
CH241: JP272.3, R582.1, U124.7
CH242: JP273.3, R581.1, U124.8
CH243: JP274.3, R580.1, U124.9
CH244: JP275.3, R579.1, U124.10
CH245: JP276.3, R578.1, U124.11
CH246: JP277.3, R577.1, U124.12
CH247: JP278.3, R576.1, U124.13
CH248: JP280.3, R602.1, U128.6
CH249: JP281.3, R601.1, U128.7
CH250: JP282.3, R600.1, U128.8
CH251: JP283.3, R599.1, U128.9
CH252: JP284.3, R598.1, U128.10
CH253: JP285.3, R597.1, U128.11
CH254: JP286.3, R596.1, U128.12
CH255: JP287.3, R595.1, U128.13
DCIN: U3.14, U4.14
DCIN1: U5.14, U6.14
DCIN2: U9.14, U10.14
DCIN3: U13.14, U14.14
DCIN4: U17.14, U18.14
DCIN5: U21.14, U22.14
DCIN6: U25.14, U26.14
DCIN7: U29.14, U30.14
DCIN8: U33.14, U34.14
DCIN9: U37.14, U38.14
DCIN10: U41.14, U42.14
DCIN11: U45.14, U46.14
DCIN12: U49.14, U50.14
DCIN13: U53.14, U54.14
DCIN14: U57.14, U58.14
DCIN15: U61.14, U62.14
DCIN16: U65.14, U66.14
DCIN17: U69.14, U70.14
DCIN18: U73.14, U74.14
DCIN19: U77.14, U78.14
DCIN20: U81.14, U82.14
DCIN21: U85.14, U86.14
DCIN22: U89.14, U90.14
DCIN23: U93.14, U94.14
DCIN24: U97.14, U98.14
DCIN25: U101.14, U102.14
DCIN26: U105.14, U106.14
DCIN27: U109.14, U110.14
DCIN28: U113.14, U114.14
DCIN29: U117.14, U118.14
DCIN30: U121.14, U122.14
DCIN31: U125.14, U126.14
FAULT: U3.19, U4.19
FAULT1: U5.19, U6.19
FAULT2: U9.19, U10.19
FAULT3: U13.19, U14.19
FAULT4: U17.19, U18.19
FAULT5: U21.19, U22.19
FAULT6: U25.19, U26.19
FAULT7: U29.19, U30.19
FAULT8: U33.19, U34.19
FAULT9: U37.19, U38.19
FAULT10: U41.19, U42.19
FAULT11: U45.19, U46.19
FAULT12: U49.19, U50.19
FAULT13: U53.19, U54.19
FAULT14: U57.19, U58.19
FAULT15: U61.19, U62.19
FAULT16: U65.19, U66.19
FAULT17: U69.19, U70.19
FAULT18: U73.19, U74.19
FAULT19: U77.19, U78.19
FAULT20: U81.19, U82.19
FAULT21: U85.19, U86.19
FAULT22: U89.19, U90.19
FAULT23: U93.19, U94.19
FAULT24: U97.19, U98.19
FAULT25: U101.19, U102.19
FAULT26: U105.19, U106.19
FAULT27: U109.19, U110.19
FAULT28: U113.19, U114.19
FAULT29: U117.19, U118.19
FAULT30: U121.19, U122.19
FAULT31: U125.19, U126.19
FW_RCVR: U3.69, U4.69
FW_RCVR1: U5.69, U6.69
FW_RCVR2: U9.69, U10.69
FW_RCVR3: U13.69, U14.69
FW_RCVR4: U17.69, U18.69
FW_RCVR5: U21.69, U22.69
FW_RCVR6: U25.69, U26.69
FW_RCVR7: U29.69, U30.69
FW_RCVR8: U33.69, U34.69
FW_RCVR9: U37.69, U38.69
FW_RCVR10: U41.69, U42.69
FW_RCVR11: U45.69, U46.69
FW_RCVR12: U49.69, U50.69
FW_RCVR13: U53.69, U54.69
FW_RCVR14: U57.69, U58.69
FW_RCVR15: U61.69, U62.69
FW_RCVR16: U65.69, U66.69
FW_RCVR17: U69.69, U70.69
FW_RCVR18: U73.69, U74.69
FW_RCVR19: U77.69, U78.69
FW_RCVR20: U81.69, U82.69
FW_RCVR21: U85.69, U86.69
FW_RCVR22: U89.69, U90.69
FW_RCVR23: U93.69, U94.69
FW_RCVR24: U97.69, U98.69
FW_RCVR25: U101.69, U102.69
FW_RCVR26: U105.69, U106.69
FW_RCVR27: U109.69, U110.69
FW_RCVR28: U113.69, U114.69
FW_RCVR29: U117.69, U118.69
FW_RCVR30: U121.69, U122.69
FW_RCVR31: U125.69, U126.69
GND: C1.2, C2.2, C3.2, JP1.1, JP2.1, JP3.1, JP4.1, JP5.1, JP6.1, JP7.1, JP8.1, JP9.1, R14.1, R15.1, R16.1, R17.1, R18.1, R19.1, U1.14, U1.23, U1.25, U2.4, U3.1, U3.5, U3.9, U3.11, U3.13, U3.15, U4.1, U4.5, U4.9, U4.11, U4.13, U4.15
GND1: C4.2, C5.2, C6.2, JP10.1, JP11.1, JP12.1, JP13.1, JP14.1, JP15.1, JP16.1, JP17.1, JP18.1, R33.1, R34.1, R35.1, R36.1, R37.1, R38.1, U5.1, U5.5, U5.9, U5.11, U5.13, U5.15, U6.1, U6.5, U6.9, U6.11, U6.13, U6.15, U7.4, U8.14, U8.23, U8.25
GND2: C7.2, C8.2, C9.2, JP19.1, JP20.1, JP21.1, JP22.1, JP23.1, JP24.1, JP25.1, JP26.1, JP27.1, R52.1, R53.1, R54.1, R55.1, R56.1, R57.1, U9.1, U9.5, U9.9, U9.11, U9.13, U9.15, U10.1, U10.5, U10.9, U10.11, U10.13, U10.15, U11.4, U12.14, U12.23, U12.25
GND3: C10.2, C11.2, C12.2, JP28.1, JP29.1, JP30.1, JP31.1, JP32.1, JP33.1, JP34.1, JP35.1, JP36.1, R71.1, R72.1, R73.1, R74.1, R75.1, R76.1, U13.1, U13.5, U13.9, U13.11, U13.13, U13.15, U14.1, U14.5, U14.9, U14.11, U14.13, U14.15, U15.4, U16.14, U16.23, U16.25
GND4: C13.2, C14.2, C15.2, JP37.1, JP38.1, JP39.1, JP40.1, JP41.1, JP42.1, JP43.1, JP44.1, JP45.1, R90.1, R91.1, R92.1, R93.1, R94.1, R95.1, U17.1, U17.5, U17.9, U17.11, U17.13, U17.15, U18.1, U18.5, U18.9, U18.11, U18.13, U18.15, U19.4, U20.14, U20.23, U20.25
GND5: C16.2, C17.2, C18.2, JP46.1, JP47.1, JP48.1, JP49.1, JP50.1, JP51.1, JP52.1, JP53.1, JP54.1, R109.1, R110.1, R111.1, R112.1, R113.1, R114.1, U21.1, U21.5, U21.9, U21.11, U21.13, U21.15, U22.1, U22.5, U22.9, U22.11, U22.13, U22.15, U23.4, U24.14, U24.23, U24.25
GND6: C19.2, C20.2, C21.2, JP55.1, JP56.1, JP57.1, JP58.1, JP59.1, JP60.1, JP61.1, JP62.1, JP63.1, R128.1, R129.1, R130.1, R131.1, R132.1, R133.1, U25.1, U25.5, U25.9, U25.11, U25.13, U25.15, U26.1, U26.5, U26.9, U26.11, U26.13, U26.15, U27.4, U28.14, U28.23, U28.25
GND7: C22.2, C23.2, C24.2, JP64.1, JP65.1, JP66.1, JP67.1, JP68.1, JP69.1, JP70.1, JP71.1, JP72.1, R147.1, R148.1, R149.1, R150.1, R151.1, R152.1, U29.1, U29.5, U29.9, U29.11, U29.13, U29.15, U30.1, U30.5, U30.9, U30.11, U30.13, U30.15, U31.4, U32.14, U32.23, U32.25
GND8: C25.2, C26.2, C27.2, JP73.1, JP74.1, JP75.1, JP76.1, JP77.1, JP78.1, JP79.1, JP80.1, JP81.1, R166.1, R167.1, R168.1, R169.1, R170.1, R171.1, U33.1, U33.5, U33.9, U33.11, U33.13, U33.15, U34.1, U34.5, U34.9, U34.11, U34.13, U34.15, U35.4, U36.14, U36.23, U36.25
GND9: C28.2, C29.2, C30.2, JP82.1, JP83.1, JP84.1, JP85.1, JP86.1, JP87.1, JP88.1, JP89.1, JP90.1, R185.1, R186.1, R187.1, R188.1, R189.1, R190.1, U37.1, U37.5, U37.9, U37.11, U37.13, U37.15, U38.1, U38.5, U38.9, U38.11, U38.13, U38.15, U39.4, U40.14, U40.23, U40.25
GND10: C31.2, C32.2, C33.2, JP91.1, JP92.1, JP93.1, JP94.1, JP95.1, JP96.1, JP97.1, JP98.1, JP99.1, R204.1, R205.1, R206.1, R207.1, R208.1, R209.1, U41.1, U41.5, U41.9, U41.11, U41.13, U41.15, U42.1, U42.5, U42.9, U42.11, U42.13, U42.15, U43.4, U44.14, U44.23, U44.25
GND11: C34.2, C35.2, C36.2, JP100.1, JP101.1, JP102.1, JP103.1, JP104.1, JP105.1, JP106.1, JP107.1, JP108.1, R223.1, R224.1, R225.1, R226.1, R227.1, R228.1, U45.1, U45.5, U45.9, U45.11, U45.13, U45.15, U46.1, U46.5, U46.9, U46.11, U46.13, U46.15, U47.4, U48.14, U48.23, U48.25
GND12: C37.2, C38.2, C39.2, JP109.1, JP110.1, JP111.1, JP112.1, JP113.1, JP114.1, JP115.1, JP116.1, JP117.1, R242.1, R243.1, R244.1, R245.1, R246.1, R247.1, U49.1, U49.5, U49.9, U49.11, U49.13, U49.15, U50.1, U50.5, U50.9, U50.11, U50.13, U50.15, U51.4, U52.14, U52.23, U52.25
GND13: C40.2, C41.2, C42.2, JP118.1, JP119.1, JP120.1, JP121.1, JP122.1, JP123.1, JP124.1, JP125.1, JP126.1, R261.1, R262.1, R263.1, R264.1, R265.1, R266.1, U53.1, U53.5, U53.9, U53.11, U53.13, U53.15, U54.1, U54.5, U54.9, U54.11, U54.13, U54.15, U55.4, U56.14, U56.23, U56.25
GND14: C43.2, C44.2, C45.2, JP127.1, JP128.1, JP129.1, JP130.1, JP131.1, JP132.1, JP133.1, JP134.1, JP135.1, R280.1, R281.1, R282.1, R283.1, R284.1, R285.1, U57.1, U57.5, U57.9, U57.11, U57.13, U57.15, U58.1, U58.5, U58.9, U58.11, U58.13, U58.15, U59.4, U60.14, U60.23, U60.25
GND15: C46.2, C47.2, C48.2, JP136.1, JP137.1, JP138.1, JP139.1, JP140.1, JP141.1, JP142.1, JP143.1, JP144.1, R299.1, R300.1, R301.1, R302.1, R303.1, R304.1, U61.1, U61.5, U61.9, U61.11, U61.13, U61.15, U62.1, U62.5, U62.9, U62.11, U62.13, U62.15, U63.4, U64.14, U64.23, U64.25
GND16: C49.2, C50.2, C51.2, JP145.1, JP146.1, JP147.1, JP148.1, JP149.1, JP150.1, JP151.1, JP152.1, JP153.1, R318.1, R319.1, R320.1, R321.1, R322.1, R323.1, U65.1, U65.5, U65.9, U65.11, U65.13, U65.15, U66.1, U66.5, U66.9, U66.11, U66.13, U66.15, U67.4, U68.14, U68.23, U68.25
GND17: C52.2, C53.2, C54.2, JP154.1, JP155.1, JP156.1, JP157.1, JP158.1, JP159.1, JP160.1, JP161.1, JP162.1, R337.1, R338.1, R339.1, R340.1, R341.1, R342.1, U69.1, U69.5, U69.9, U69.11, U69.13, U69.15, U70.1, U70.5, U70.9, U70.11, U70.13, U70.15, U71.4, U72.14, U72.23, U72.25
GND18: C55.2, C56.2, C57.2, JP163.1, JP164.1, JP165.1, JP166.1, JP167.1, JP168.1, JP169.1, JP170.1, JP171.1, R356.1, R357.1, R358.1, R359.1, R360.1, R361.1, U73.1, U73.5, U73.9, U73.11, U73.13, U73.15, U74.1, U74.5, U74.9, U74.11, U74.13, U74.15, U75.4, U76.14, U76.23, U76.25
GND19: C58.2, C59.2, C60.2, JP172.1, JP173.1, JP174.1, JP175.1, JP176.1, JP177.1, JP178.1, JP179.1, JP180.1, R375.1, R376.1, R377.1, R378.1, R379.1, R380.1, U77.1, U77.5, U77.9, U77.11, U77.13, U77.15, U78.1, U78.5, U78.9, U78.11, U78.13, U78.15, U79.4, U80.14, U80.23, U80.25
GND20: C61.2, C62.2, C63.2, JP181.1, JP182.1, JP183.1, JP184.1, JP185.1, JP186.1, JP187.1, JP188.1, JP189.1, R394.1, R395.1, R396.1, R397.1, R398.1, R399.1, U81.1, U81.5, U81.9, U81.11, U81.13, U81.15, U82.1, U82.5, U82.9, U82.11, U82.13, U82.15, U83.4, U84.14, U84.23, U84.25
GND21: C64.2, C65.2, C66.2, JP190.1, JP191.1, JP192.1, JP193.1, JP194.1, JP195.1, JP196.1, JP197.1, JP198.1, R413.1, R414.1, R415.1, R416.1, R417.1, R418.1, U85.1, U85.5, U85.9, U85.11, U85.13, U85.15, U86.1, U86.5, U86.9, U86.11, U86.13, U86.15, U87.4, U88.14, U88.23, U88.25
GND22: C67.2, C68.2, C69.2, JP199.1, JP200.1, JP201.1, JP202.1, JP203.1, JP204.1, JP205.1, JP206.1, JP207.1, R432.1, R433.1, R434.1, R435.1, R436.1, R437.1, U89.1, U89.5, U89.9, U89.11, U89.13, U89.15, U90.1, U90.5, U90.9, U90.11, U90.13, U90.15, U91.4, U92.14, U92.23, U92.25
GND23: C70.2, C71.2, C72.2, JP208.1, JP209.1, JP210.1, JP211.1, JP212.1, JP213.1, JP214.1, JP215.1, JP216.1, R451.1, R452.1, R453.1, R454.1, R455.1, R456.1, U93.1, U93.5, U93.9, U93.11, U93.13, U93.15, U94.1, U94.5, U94.9, U94.11, U94.13, U94.15, U95.4, U96.14, U96.23, U96.25
GND24: C73.2, C74.2, C75.2, JP217.1, JP218.1, JP219.1, JP220.1, JP221.1, JP222.1, JP223.1, JP224.1, JP225.1, R470.1, R471.1, R472.1, R473.1, R474.1, R475.1, U97.1, U97.5, U97.9, U97.11, U97.13, U97.15, U98.1, U98.5, U98.9, U98.11, U98.13, U98.15, U99.4, U100.14, U100.23, U100.25
GND25: C76.2, C77.2, C78.2, JP226.1, JP227.1, JP228.1, JP229.1, JP230.1, JP231.1, JP232.1, JP233.1, JP234.1, R489.1, R490.1, R491.1, R492.1, R493.1, R494.1, U101.1, U101.5, U101.9, U101.11, U101.13, U101.15, U102.1, U102.5, U102.9, U102.11, U102.13, U102.15, U103.4, U104.14, U104.23, U104.25
GND26: C79.2, C80.2, C81.2, JP235.1, JP236.1, JP237.1, JP238.1, JP239.1, JP240.1, JP241.1, JP242.1, JP243.1, R508.1, R509.1, R510.1, R511.1, R512.1, R513.1, U105.1, U105.5, U105.9, U105.11, U105.13, U105.15, U106.1, U106.5, U106.9, U106.11, U106.13, U106.15, U107.4, U108.14, U108.23, U108.25
GND27: C82.2, C83.2, C84.2, JP244.1, JP245.1, JP246.1, JP247.1, JP248.1, JP249.1, JP250.1, JP251.1, JP252.1, R527.1, R528.1, R529.1, R530.1, R531.1, R532.1, U109.1, U109.5, U109.9, U109.11, U109.13, U109.15, U110.1, U110.5, U110.9, U110.11, U110.13, U110.15, U111.4, U112.14, U112.23, U112.25
GND28: C85.2, C86.2, C87.2, JP253.1, JP254.1, JP255.1, JP256.1, JP257.1, JP258.1, JP259.1, JP260.1, JP261.1, R546.1, R547.1, R548.1, R549.1, R550.1, R551.1, U113.1, U113.5, U113.9, U113.11, U113.13, U113.15, U114.1, U114.5, U114.9, U114.11, U114.13, U114.15, U115.4, U116.14, U116.23, U116.25
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
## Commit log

2014-08-06 Add version info
2014-08-06 Touch up silk, resistor placement
2014-08-06 Increased length of board by 100th
2014-08-06 Skootch resistors out of keepout region.
2014-08-07 Move resistors and traces out of restrict zone
2014-08-08 Incorporate review changes
2014-08-11 Add fids
2014-08-12 Fix fids, remove weird name
2014-09-24 Added DCIN pin Corrected Header footprint Renamed board and files Cleaned up dimensions and added units Added VSYS -> VIN circuit Added DNP to pullup resistors
2014-10-16 Rev to 10. Fix gnd and pwr, text
2014-10-17 Touch up packages, silk for reds
2014-10-17 Ready for reds Thicken VSYS->VIN trace Fix a stray ground thermal on PCA9306 No known to-do items
2014-10-22 created v10 panels
2015-04-01 Updating README and directory names
